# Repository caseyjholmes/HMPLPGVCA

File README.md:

# HMPLPGVCA
Holmes Modular 2HP passive vactrol LPG/VCA circuit

My take on the passive vactrol VCA/LPG. I used VTL5C4 but you can experiment with different components. I'd suggest some home made vactrols as well, to test different sounds. You may use pluggable socket pins in the vactrol slot so you can plug different vactrols in and out. You may also swap resistors and capacitors for varried effect.
-Casey

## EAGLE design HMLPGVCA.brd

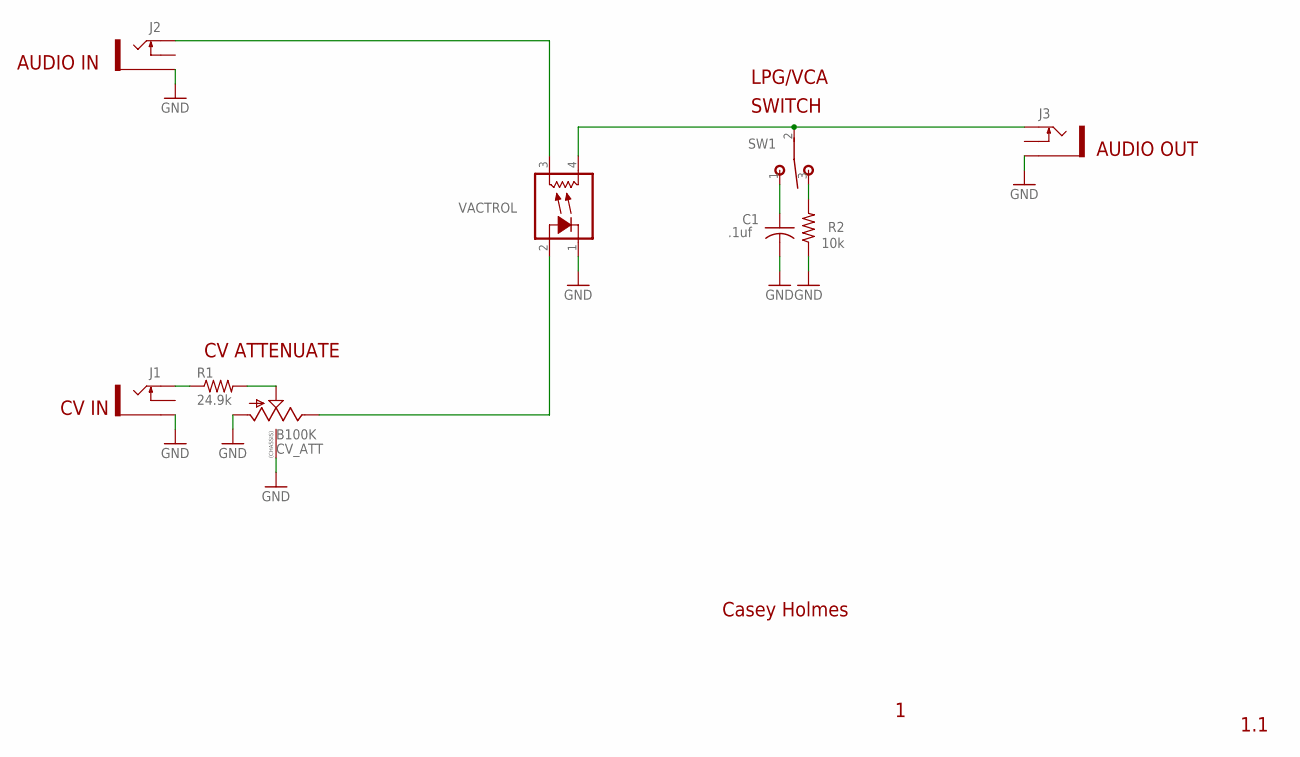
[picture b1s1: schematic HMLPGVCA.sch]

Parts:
C1: .1uf; C0805K
CV_ATT: B100K; 9MM_SNAP-IN_POT
J1, J2, J3: THONKICONNNEW; WQP-PJ301M-12_JACK
R1: 24.9k; R0805
R2: 10k; R0805
SW1: T-80-T-SPDT-ON-OFF-ON; M9040P
VACTROL: VACTROL; VACTROL_4PIN_VTL5C

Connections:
GND: C1.2, CV_ATT.1 (A), CV_ATT.CHASSIS1, CV_ATT.CHASSIS2, J1.P$3_SLEEVE (SLEEVE), J2.P$3_SLEEVE (SLEEVE), J3.P$3_SLEEVE (SLEEVE), R2.1, VACTROL.1 (LED-)
unnamed: J1.P$1_TIP (TIP), R1.1
unnamed: CV_ATT.2 (S), R1.2
unnamed: CV_ATT.3 (E), VACTROL.2 (LED+)
unnamed: R2.2, SW1.3 (S)
unnamed: C1.1, SW1.1 (O)
unnamed: J3.P$1_TIP (TIP), SW1.2, VACTROL.4 (RES2)
unnamed: J2.P$1_TIP (TIP), VACTROL.3 (RES1)

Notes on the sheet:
CV IN
AUDIO IN
AUDIO OUT
LPG/VCA
SWITCH
CV ATTENUATE
1.1
Casey Holmes

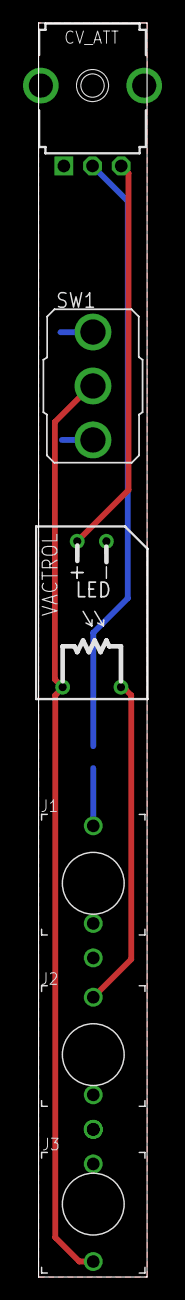
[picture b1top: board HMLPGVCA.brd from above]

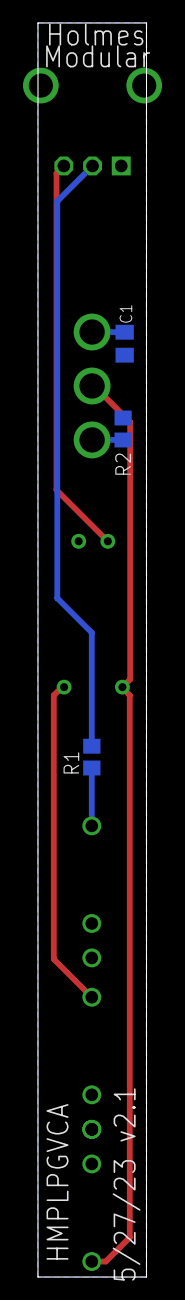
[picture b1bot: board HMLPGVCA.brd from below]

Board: 2 copper layers, 9.4 x 109.2 mm, 9 parts (3 on the bottom side), 8 nets.
